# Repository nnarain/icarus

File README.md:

# Icarus Flight Controller

Icarus is a controller for robotics applications.

Firmware is located [here](https://github.com/nnarain/icarus-firmware).

Features:

* Controls 4 DC brushed motors
* IMU (gyro/accelerometer/temperature)
* Barometer
* USB Serial
* Battery sense
* 30.5 x 30.5 millimeter mounting holes (for drones).

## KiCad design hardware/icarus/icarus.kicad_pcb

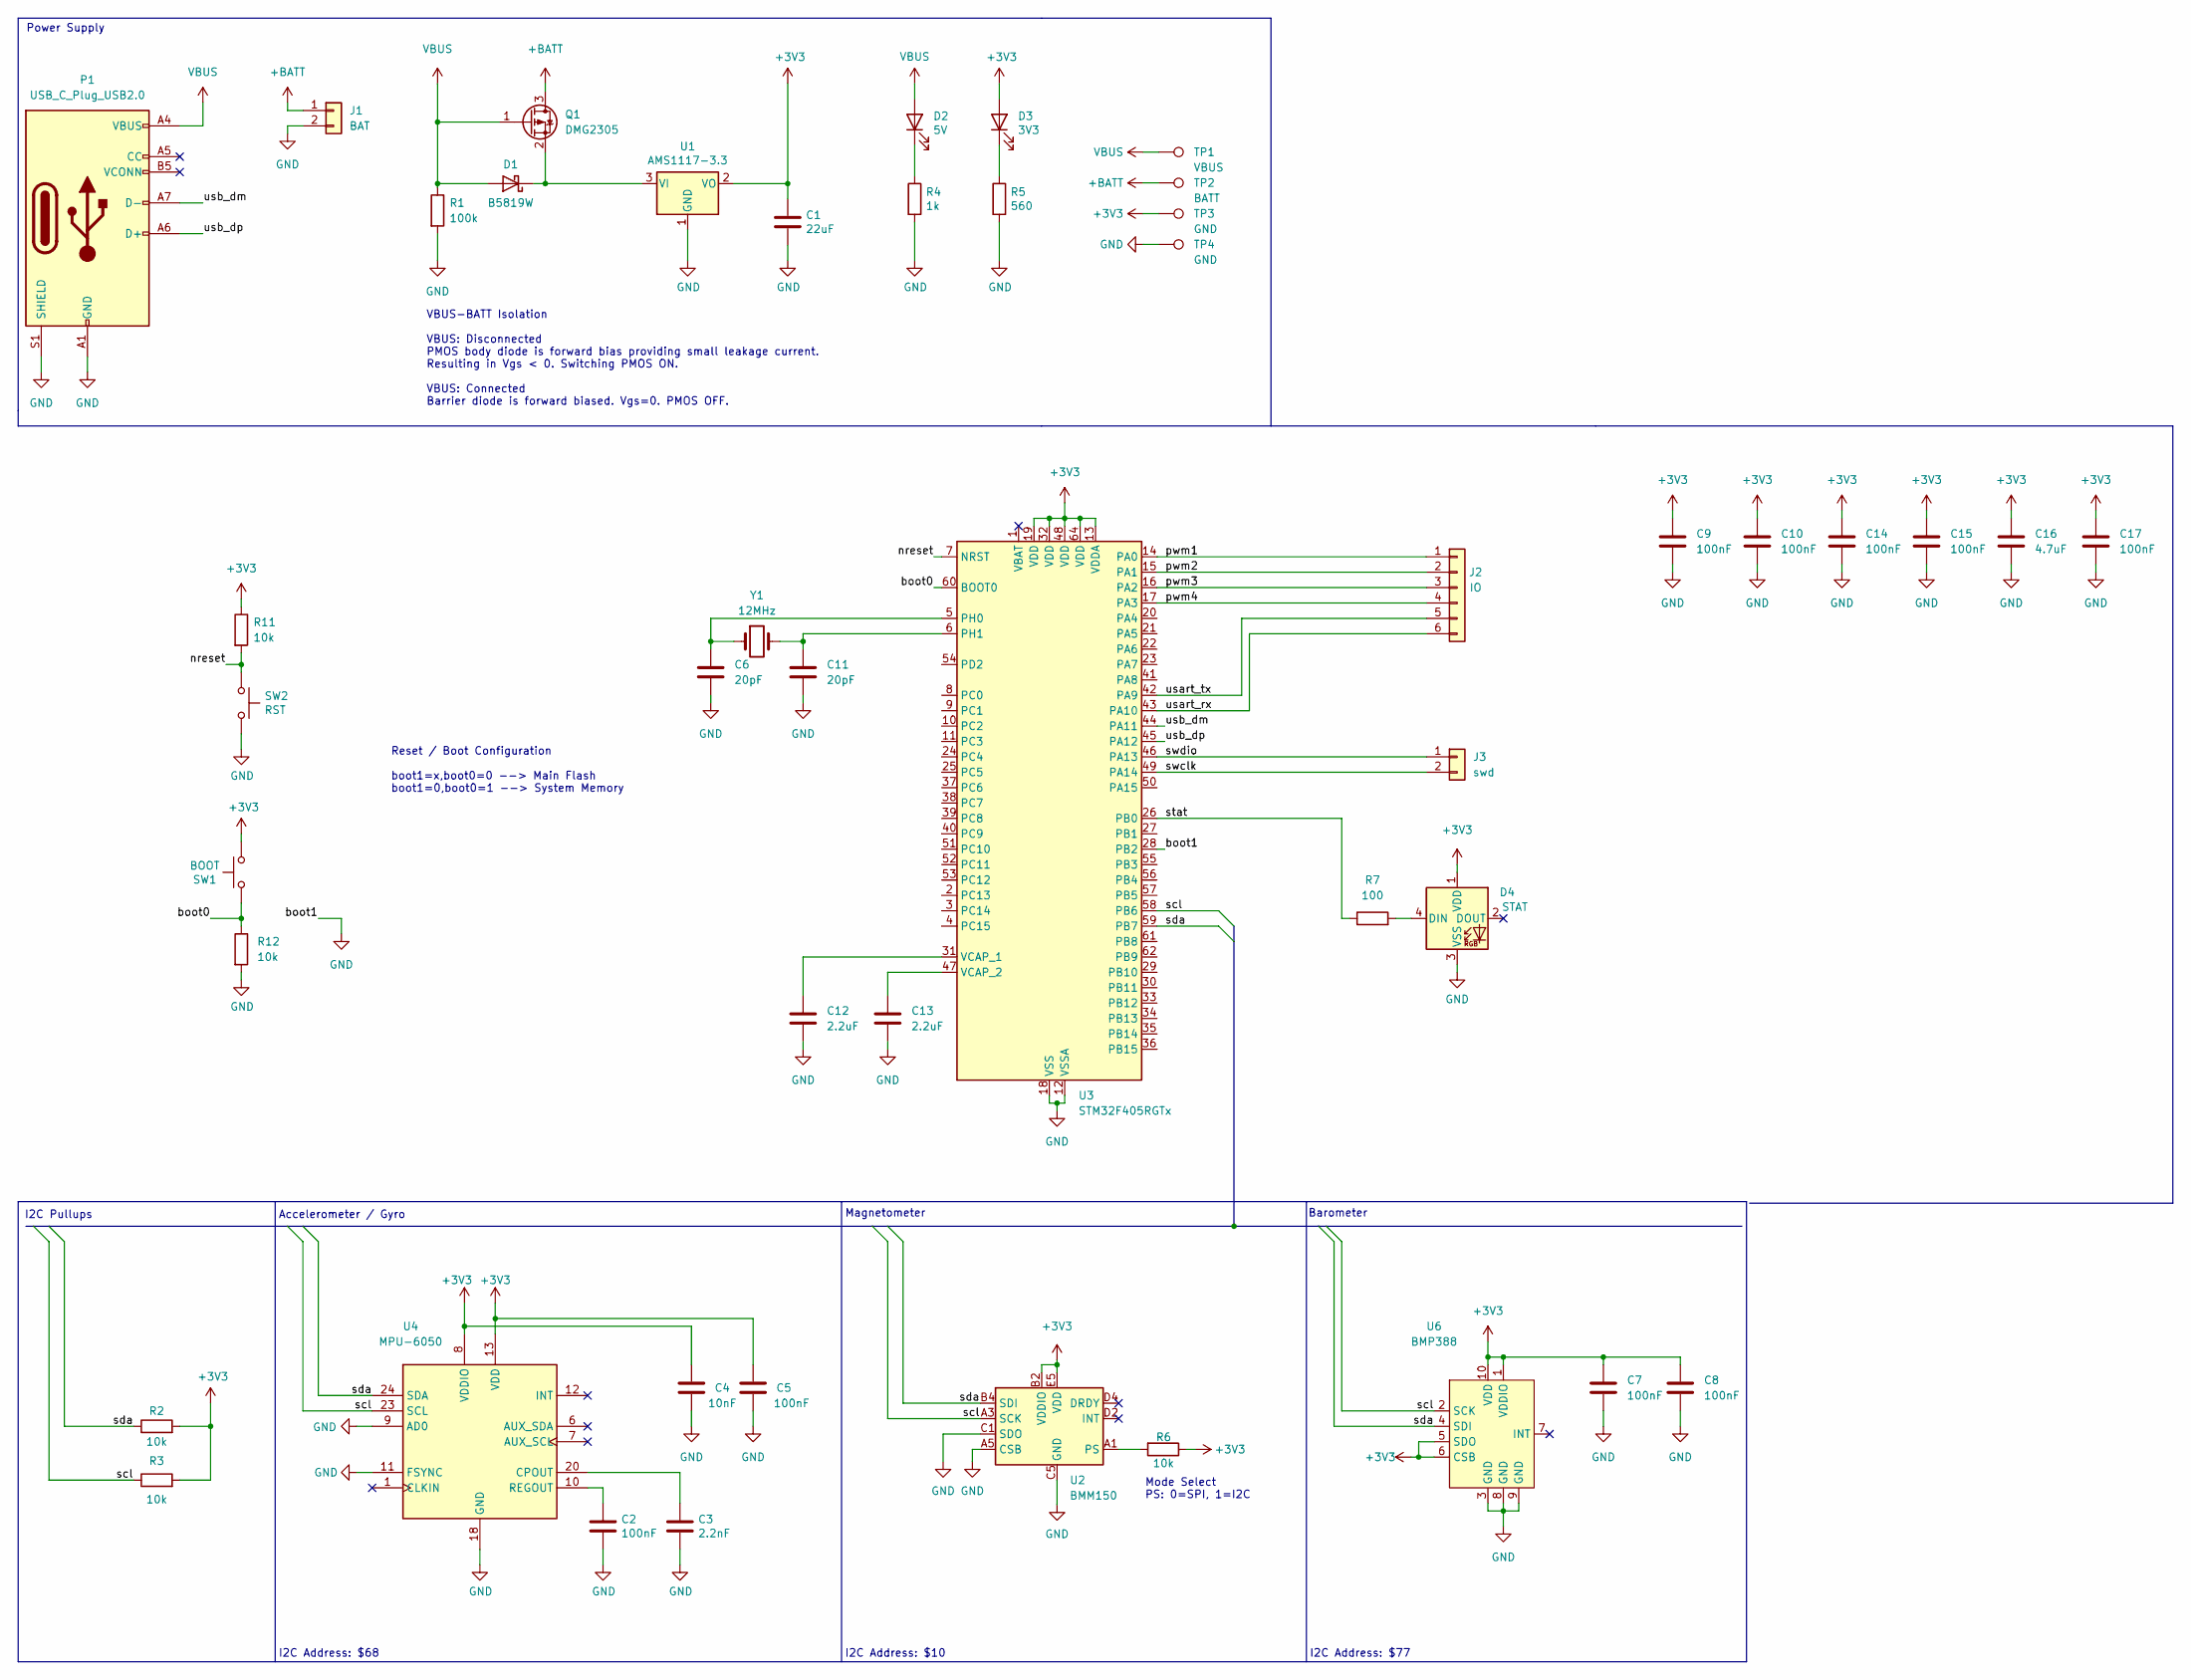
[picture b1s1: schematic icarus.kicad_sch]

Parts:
C1: 22uF; CP_EIA-3216-18_Kemet-A; LCSC C116575
C2, C5, C7, C8, C9, C10, C14, C15, C17: 100nF; C_0402_1005Metric; LCSC C307331
C3: 2.2nF; C_0402_1005Metric; LCSC C1531
C4: 10nF; C_0402_1005Metric; LCSC C15195
C6, C11: 20pF; C_0402_1005Metric; LCSC C1554
C12, C13: 2.2uF; C_0402_1005Metric; LCSC C12530
C16: 4.7uF; C_0402_1005Metric; LCSC C23733
D1: B5819W; D_SOD-123; LCSC C8598
D2: 5V; LED_0805_2012Metric; LCSC C434432
D3: 3V3; LED_0805_2012Metric; LCSC C434432
D4: STAT; LED_WS2812B_PLCC4_5.0x5.0mm_P3.2mm; LCSC C2761795
J1: BAT; PinHeader_1x02_P2.54mm_Vertical
J2: IO; PinHeader_1x06_P2.54mm_Vertical
J3: swd; PinHeader_1x02_P1.00mm_Vertical
P1: USB_C_Plug_USB2.0; TYPE-C-31-M-04; LCSC C129018
Q1: DMG2305; SOT-23; LCSC C150470
R1: 100k; R_0402_1005Metric; LCSC C25741
R2, R3, R6, R11, R12: 10k; R_0402_1005Metric; LCSC C25744
R4: 1k; R_0402_1005Metric; LCSC C25543
R5: 560; R_0402_1005Metric; LCSC C25172
R7: 100; R_0402_1005Metric; LCSC C25076
SW1: BOOT; TS-1088-AR02016; LCSC C720477
SW2: RST; TS-1088-AR02016; LCSC C720477
TP1: VBUS; TestPoint_Pad_1.0x1.0mm
TP2: BATT; TestPoint_Pad_1.0x1.0mm
TP3, TP4: GND; TestPoint_Pad_1.0x1.0mm
U1: AMS1117-3.3; SOT-223-3_TabPin2; LCSC C6186
U2: BMM150; WLCSP-12_1.56x1.56mm_P0.4mm; LCSC C171681
U3: STM32F405RGTx; LQFP-64_10x10mm_P0.5mm
U4: MPU-6050; InvenSense_QFN-24_4x4mm_P0.5mm; LCSC C24112
U6: BMP388; LCSC C779278
Y1: 12MHz; Crystal_SMD_3225-4Pin_3.2x2.5mm; LCSC C9002

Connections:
+3V3: C1.1, C4.2, C5.2, C7.1, C8.1, C9.1, C10.1, C14.1, C15.1, C16.1, C17.1, D3.2 (A), D4.1 (VDD), R2.2, R3.2, R6.1, R11.1, SW1.2, TP3.1, U1.2 (VO), U2.B2 (VDDIO), U2.E5 (VDD), U3.13 (VDDA), U3.19 (VDD), U3.32 (VDD), U3.48 (VDD), U3.64 (VDD), U4.8 (VDDIO), U4.13 (VDD), U6.1 (VDDIO), U6.5 (SDO), U6.6 (CSB), U6.10 (VDD)
+BATT: J1.1, Q1.3 (D), TP2.1
/boot0: R12.1, SW1.1, U3.60 (BOOT0)
/nreset: R11.2, SW2.1, U3.7 (NRST); also elsewhere on the board
/pwm1: J2.1, U3.14 (PA0)
/pwm2: J2.2, U3.15 (PA1)
/pwm3: J2.3, U3.16 (PA2)
/pwm4: J2.4, U3.17 (PA3)
/scl: R3.1, U2.A3 (SCK), U3.58 (PB6), U4.23 (SCL), U6.2 (SCK)
/sda: R2.1, U2.B4 (SDI), U3.59 (PB7), U4.24 (SDA), U6.4 (SDI)
/stat: R7.1, U3.26 (PB0)
/swclk: J3.2, U3.49 (PA14)
/swdio: J3.1, U3.46 (PA13)
/usart_rx: J2.6, U3.43 (PA10)
/usart_tx: J2.5, U3.42 (PA9)
/usb_dm: P1.A7 (D-), U3.44 (PA11)
/usb_dp: P1.A6 (D+), U3.45 (PA12)
GND: C1.2, C2.2, C3.2, C4.1, C5.1, C6.2, C7.2, C8.2, C9.2, C10.2, C11.2, C12.2, C13.2, C14.2, C15.2, C16.2, C17.2, D4.3 (VSS), J1.2, P1.A1 (GND), P1.A12 (GND), P1.B1 (GND), P1.B12 (GND), P1.S1 (SHIELD), R1.2, R4.2, R5.2, R12.2, SW2.2, TP4.1, U1.1 (GND), U2.A5 (CSB), U2.C1 (SDO), U2.C5 (GND), U2.E1 (GND), U2.E3 (GND), U3.12 (VSSA), U3.18 (VSS), U3.28 (PB2), U3.63 (VSS), U4.9 (AD0), U4.11 (FSYNC), U4.18 (GND), U6.3 (GND), U6.8 (GND), U6.9 (GND); also elsewhere on the board
unnamed: D1.1 (K), Q1.2 (S), U1.3 (VI)
unnamed: D2.1 (K), R4.1
unnamed: D3.1 (K), R5.1
unnamed: D4.4 (DIN), R7.2
unnamed: R6.2, U2.A1 (PS)
unnamed: C6.1, U3.5 (PH0), Y1.1
unnamed: C11.1, U3.6 (PH1), Y1.2
unnamed: C12.1, U3.31 (VCAP_1)
unnamed: C13.1, U3.47 (VCAP_2)
unnamed: C3.1, U4.20 (CPOUT)
unnamed: C2.1, U4.10 (REGOUT)
VBUS: D1.2 (A), D2.2 (A), P1.A4 (VBUS), P1.A9 (VBUS), P1.B4 (VBUS), P1.B9 (VBUS), Q1.1 (G), R1.1, TP1.1

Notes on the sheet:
I2C Address: $77
Barometer
I2C Address: $68
I2C Address: $10
I2C Pullups
VBUS-BATT Isolation VBUS: Disconnected PMOS body diode is forward bias providing small leakage current. Resulting in Vgs < 0. Switching PMOS ON. VBUS: Connected Barrier diode is forward biased. Vgs=0. PMOS OFF.
Accelerometer / Gyro
Mode Select PS: 0=SPI, 1=I2C
Magnetometer
Reset / Boot Configuration boot1=x,boot0=0 --> Main Flash boot1=0,boot0=1 --> System Memory
Power Supply

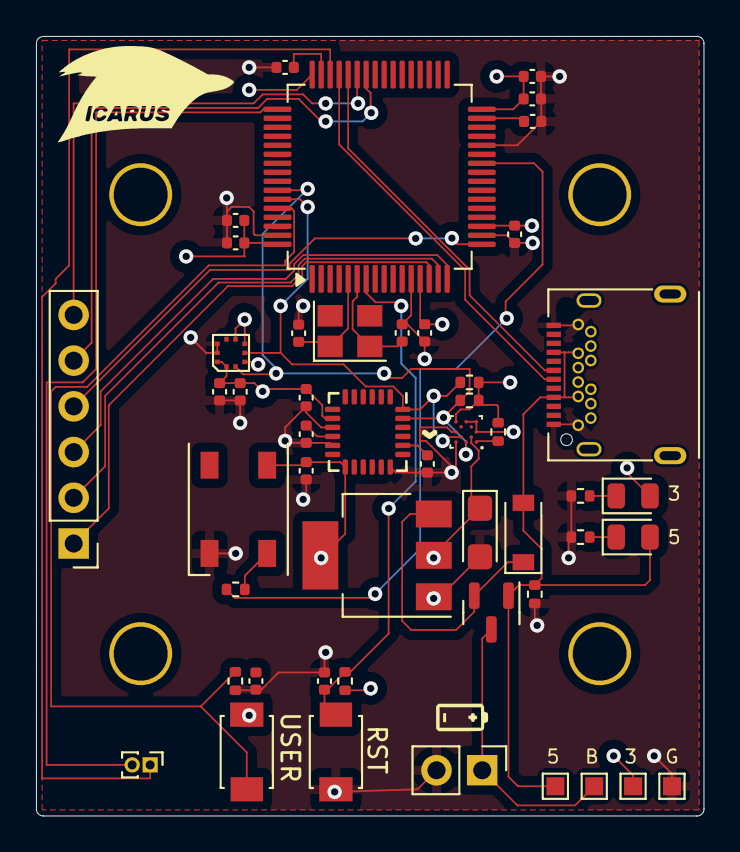
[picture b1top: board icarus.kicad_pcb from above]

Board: 4 copper layers, 37.1 x 43.3 mm, 49 parts (0 on the bottom side), 30 nets.

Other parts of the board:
C9#2, C10#2: 100nF; C_0402_1005Metric

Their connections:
/nreset: C9#2.1; also elsewhere on the board
GND: C9#2.2, C10#2.2; also elsewhere on the board

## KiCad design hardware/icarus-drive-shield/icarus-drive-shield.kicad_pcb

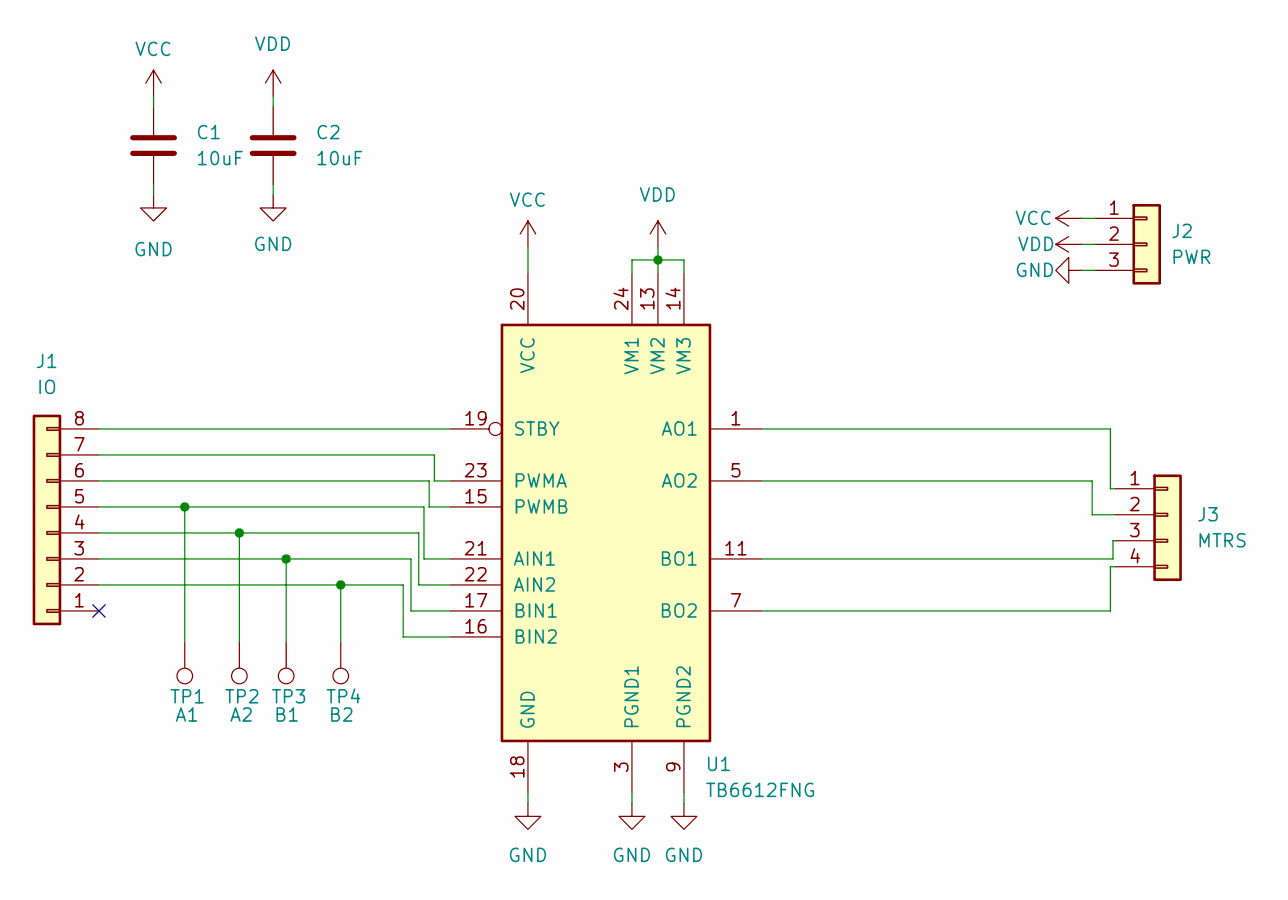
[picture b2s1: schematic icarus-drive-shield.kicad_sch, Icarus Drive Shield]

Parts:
C1, C2: 10uF; C_0805_2012Metric; LCSC C440198
J1: IO; PinHeader_1x08_P2.54mm_Vertical
J2: PWR; PinHeader_1x03_P2.54mm_Vertical
J3: MTRS; PinHeader_1x04_P2.54mm_Vertical
TP1: A1; TestPoint_Pad_2.0x2.0mm
TP2: A2; TestPoint_Pad_2.0x2.0mm
TP3: B1; TestPoint_Pad_2.0x2.0mm
TP4: B2; TestPoint_Pad_2.0x2.0mm
U1: TB6612FNG; SSOP-24_5.3x8.2mm_P0.65mm; LCSC C88224

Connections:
GND: C1.2, C2.2, J2.3, U1.3 (PGND1), U1.4 (PGND1), U1.9 (PGND2), U1.10 (PGND2), U1.18 (GND)
unnamed 1: J1.2, TP4.1, U1.16 (BIN2); also elsewhere on the board
unnamed 2: J1.3, TP3.1, U1.17 (BIN1); also elsewhere on the board
unnamed 3: J1.4, TP2.1, U1.22 (AIN2); also elsewhere on the board
unnamed 7: J1.8, U1.19 (STBY); also elsewhere on the board
unnamed: J3.1, U1.1 (AO1), U1.2 (AO1)
unnamed: J3.2, U1.5 (AO2), U1.6 (AO2)
unnamed: J3.4, U1.7 (BO2), U1.8 (BO2)
unnamed: J3.3, U1.11 (BO1), U1.12 (BO1)
unnamed: J1.6, U1.15 (PWMB)
unnamed: J1.5, TP1.1, U1.21 (AIN1)
unnamed: J1.7, U1.23 (PWMA)
VCC: C1.1, J2.1, U1.20 (VCC)
VDD: C2.1, J2.2, U1.13 (VM2), U1.14 (VM3), U1.24 (VM1)

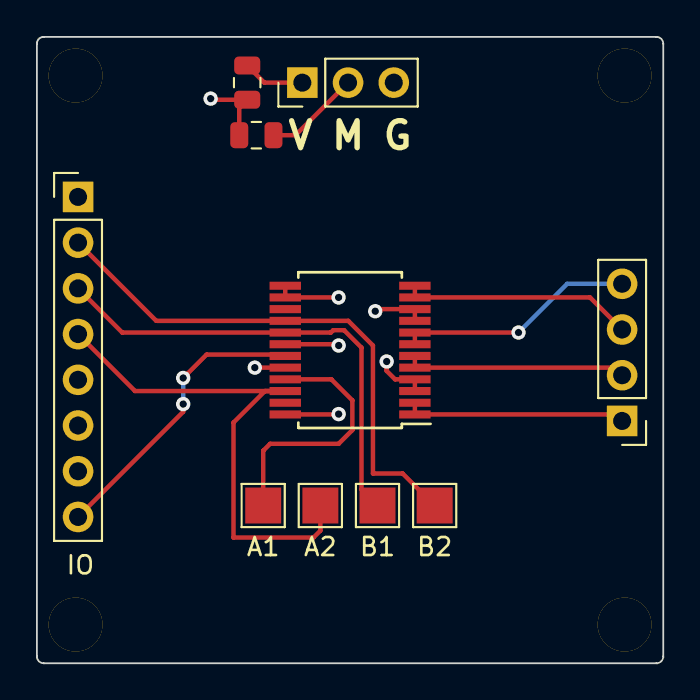
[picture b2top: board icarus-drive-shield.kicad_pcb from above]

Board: 4 copper layers, 34.8 x 34.8 mm, 10 parts (0 on the bottom side), 12 nets.

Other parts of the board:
IO: IO; PinHeader_1x08_P2.54mm_Vertical

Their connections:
unnamed 1: IO.2; also elsewhere on the board
unnamed 2: IO.3; also elsewhere on the board
unnamed 3: IO.4; also elsewhere on the board
unnamed 7: IO.8; also elsewhere on the board

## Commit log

2021-11-06 Design with stm32f3
2021-11-06 Switch linear regulator
2021-11-08 Add README
2021-12-03 Layer update
2021-12-03 Resolves #7. Add README image
2021-12-03 Resolves #7. Added image to readme
2021-12-04 Actually add image...
2021-12-04 Resolves #2, #9, #10. Test points, USART1 Labels, IMU AD0 pint.
2021-12-04 Resolves #4. Increased resistor values for LEDs
2022-01-28 Kicad 6 Update
2022-01-30 Resolves #3, #13. Use 5 pin header for SWD, Use SOT-89 package for regulator.
2022-01-30 Resolves #5. Smaller push buttons for BOOT and RST
2022-01-30 Resolves #1. Micro USB footprint selection
2022-02-10 Resolves #6, #17, #18. Resize and routing. Added barometer.
2022-02-12 Added LCSC to BMP on schematic
2022-02-21 kibot ci
2022-02-21 pathes
2022-02-21 disable checks
2022-02-22 Resolves #8. KiCAD CI
2022-02-26 Resolves #21. Project docs
2022-02-26 Add manual workflow dispatch
2022-02-26 deploy: aec50520e900ec1680cb7fdc3760dfca38bf84e6
2022-04-07 Resolves #20. BoM for JLCPCB
2022-05-21 Added Makefile
2022-06-16 Update kicad-inventory
2022-06-29 Rev C
2022-07-10 deploy: 00b4df2714c4c3e42d6f4d0f0187f2219e085705
2022-08-08 Initial frame design
2022-08-28 Adjust frame values
2023-01-16 Drive shield
2023-01-26 Rev D
2023-01-26 deploy: d8488512114c6dc494ebeb9a1dd19d99a7c46c1f
2023-04-07 update docs
2023-04-07 deploy: 12f72e5eab07b8d7ebd24d38ed177edd5958b420
2023-04-07 Update diagram
2023-04-07 deploy: 4b37f99d30cf360ccb3220dc34c28f52b665acc5
2023-04-19 Rev D.2
2023-04-19 deploy: 673112852671bd3c9d503c3c8cf4281da9bbda74
2023-10-06 kicad 7
2024-06-16 Update actions
2024-06-16 Update workflow to use github token
2024-06-16 deploy: 4d711a23bbf5aa3d2fd8e02f7bb7476df0587360
2024-06-16 add stm32 lcsc number
2024-06-16 deploy: 4671fadeaaa527561b8c0b979b1bb24e9cfa5f85
2024-06-16 update banner
2024-06-16 deploy: 3ee73bf868b0a3ec514a8e68d844691be0917cfd
